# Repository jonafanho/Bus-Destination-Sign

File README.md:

# Bus Destination Sign
A simulation of LED or flip dot bus destination signs using the STM32 Blue Pill.

## Quick Start
### First Run
1. Insert an empty micro SD card (formatted to FAT32) into the SD card slot.
1. Power up the STM32 microcontroller using a Micro USB cable.
1. After the system finishes loading, the screen will turn black. The necessary folders and configuration files will be automatically set up on the SD card.
1. Turn off the microcontroller by unplugging the Micro USB cable, then remove the SD card from the SD card slot.

### Adding Images
1. On a computer, download or obtain images to be shown on the destination signs. Some good sites include [HKBRDA](https://www.hkbrda.org/rddc/main.php) and [Stopreporter](https://sites.google.com/site/stopreporter2003/edisplay).
1. Convert all images into the BMP file format. [Online converter](https://image.online-convert.com/convert-to-bmp) is an easy site to convert images quickly.
1. Open the SD card on the computer. Inside the SD card, you should see the following folders:
   * In the root directory, there should be ten folders named `0` to `9`. These folders group images of the same bus routes together.
   * In each of the ten folders, there should be three folders named `front`, `side`, and `back`. These folders designate which images appear on the front, side, and rear displays.
   * If these folders don't exist, follow the [First Run](#first-run) steps above to automatically create the necessary folders and configuration files.
1. Copy the BMP files to any of the `front`, `side`, or `back` folders on the SD card.
   * Images of the same bus route should be grouped together.
   * Images of the front, side, and back displays should go into their respective folders.
   * An example of the SD card file structure is shown [below](#example-sd-card-file-structure).
1. Safely eject the SD card from the computer and reinsert the SD card to the SD card slot.
1. Power up the STM32 microcontroller again.
   * The images from `0/front`, `0/side`, and `0/back` should show up on the front, side, and back displays respectively.
   * On the device or a connected remote, press the button to change routes. The images from `1/front`, `1/side`, and `1/back` should now show up.
   * Pressing the button again should cycle thorugh the routes. Note that if all three `front`, `side`, and `back` folders of a group is empty, the group will be skipped.

### Example SD Card File Structure
```
root
├───global_settings.txt
├───0
│   ├───image_settings.txt
│   ├───front
│   │   ├───KMB-74X-00.bmp
│   │   └───KMB-74X-01.bmp
│   ├───side
│   │   └───KMB-74X-10.bmp
│   └───back
│       └───KMB-74X-20.bmp
├───1
│   ├───image_settings.txt
│   ├───front
│   │   ├───KMB-680-00.bmp
│   │   ├───KMB-680-01.bmp
│   │   └───KMB-680-02.bmp
│   ├───side
│   │   ├───KMB-680-10.bmp
│   │   └───KMB-680-11.bmp
│   └───back
│       ├───KMB-680-20.bmp
│       └───KMB-680-21.bmp
...
└───9
    ├───image_settings.txt
    ├───front
    │   └───KMB-special-00.bmp
    ├───side
    └───back
```

## Configuration
There are two types of settings that can be configured by the user. All fields accept positive integers. If a corrupted settings file is detected, it will be reset to its default values.

### Global Settings
These settings control the display animation as a whole. The configuration file, `global_settings.txt`, is in the root of the SD card.

The contents of `global_settings.txt` with its default values are shown below.
```
scroll_animation=1
switch_delay=2
```
Parameter | Description
--- | ---
`scroll_animation` | Defines whether a scrolling animation will be used when switching between images. The scrolling animation simulates flip dot displays.<br>`scroll_animation=0`: No scrolling animation<br>`scroll_animation=1`: Scrolling animation
`switch_delay` | The amount of time (in seconds) to show each image before switching to the next one.<br>Note: The actual time might be greater than the number specified here depending on the time it takes to load the next image.

### Image Settings
These settings control the way images are scaled or cropped. The configuration file, `image_settings.txt`, is inside each of the ten folders `0` to `9` on the SD card.

"Scale" refers to how many pixels (in one axis) on the BMP image maps to one pixel (in one axis) on the physical display. For example, a scale of 3 means that every 3x3 square on the BMP image corresponds to one pixel on the physical display.

"Crop" refers to how many pixels (symmetrical on all sides) of the BMP image will not be shown on the physical display.

The contents of `image_settings.txt` with its default values are shown below.
```
front_scale=3
front_crop=20
side_scale=3
side_crop=19
back_scale=1
back_crop=0
```
Parameter | Description
--- | ---
`front_scale` | The scaling of the images on the front display.
`front_crop` | The crop of the images on the front display.
`side_scale` | The scaling of the images on the side display.
`side_crop` | The crop of the images on the side display.
`back_scale` | The scaling of the images on the back display.
`back_crop` | The crop of the images on the back display.

## Special Scrolling
To use special scrolling on an image, the file name must begin with an exclamation mark (`!`).

After the exclamation mark, the file name should contain a three digit number. This number corresponds to the number of pixels from the left edge (after scaling) where the image should be split. The pixels before the split to the left will display as a stationary image, and the pixels on or after the split to the right will be scrolled. If the number is less than three digits long, it should be padded by zeros.

An example of file names implementing special scrolling is shown below.
```
!046-NWFB-682.bmp
!112-NWFB-15.bmp
```

## Troubleshooting
* My images are not showing up!
  * Make sure the images are in BMP format. (8, 16, 24, and 32-bit uncompressed BMP files are supported.)
  * Make sure the BMP files are in any of the three folders (front, side, or back). They shouldn't be anywhere else or nested inside those folders.
  * Make sure the image crop value is low enough that at least a part of the image is still visible.
* My images take forever to load!
  * Keep the image sizes small, preferably smaller than 500x500 pixels.
  * Images will load slower for the first time as the cache is being created.
* My SD card failed to initalize!
  * Make sure the SD card is formatted to FAT32.
  * Make sure the SD card is clean, inserted fully into the SD card slot, and oriented in the correct direction.

## Building it Yourself
Refer to the [Installation](https://github.com/jonafanho/Bus-Destination-Sign/blob/master/Installation.md) page for instructions.

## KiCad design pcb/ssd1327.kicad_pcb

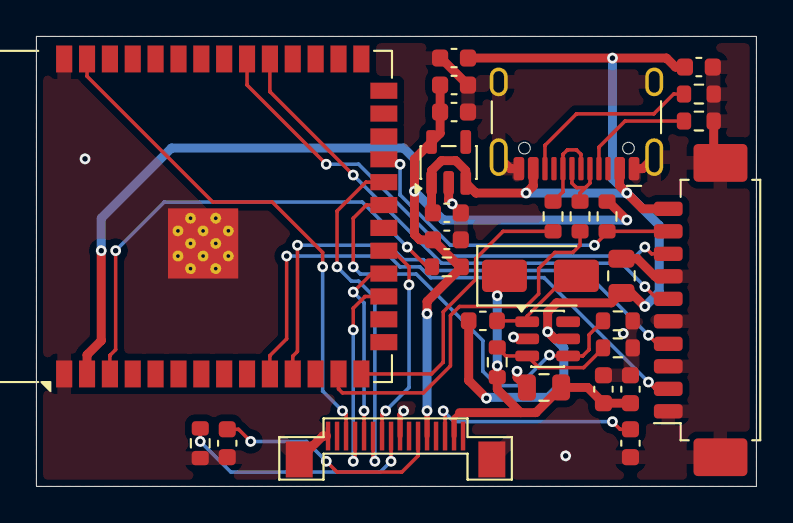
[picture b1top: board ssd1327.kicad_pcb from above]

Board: 2 copper layers, 40.0 x 25.0 mm, 30 parts (0 on the bottom side), 27 nets.

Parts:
C1, C5: 1uF; C_0603_1608Metric
C2: 4.7uF; C_0603_1608Metric
C3, C7, C11: 10uF; C_0603_1608Metric
C4, C8, C12: 0.1uF; C_0603_1608Metric
C6: 2.2uF; C_0603_1608Metric
C9, C10: 22uF; C_0805_2012Metric
D1: SS34; D_SMA
J1: Display Connector Input; Molex_PicoBlade_53261-1071_1x10-1MP_P1.25mm_Horizontal
J2: SSD1327 16-Pin Connector; 16-pin
J3: USB_C_Receptacle_USB2.0_16P; USB_C_Receptacle_HCTL_HC-TYPE-C-16P-01A
L1: 10uH; L_0603_1608Metric
R1, R7, R10: 10k; R_0603_1608Metric
R2: 1M; R_0603_1608Metric
R3, R4: 5.1k; R_0603_1608Metric
R5, R6: 22R; R_0603_1608Metric
R8: 100k; R_0603_1608Metric
R9: 200k; R_0603_1608Metric
U1: AP2112K-3.3; SOT-23-5
U2: ESP32-S3-WROOM-1
U3: MT3608; SOT-23-6

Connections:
+5V: C3.1, C4.1, C5.1, C9.1, J1.10 (5V), J3.A4 (VBUS), J3.A9 (VBUS), J3.B4 (VBUS), J3.B9 (VBUS), L1.1, U1.1 (VIN), U1.3 (EN), U3.5 (IN)
/ESP32 for SSD1327/3V3: C6.1, C7.1, C8.1, J2.5 (VCI), R1.1, R7.1, U1.5 (VOUT), U2.2 (3V3)
/ESP32 for SSD1327/CLK: J1.2 (CLK), U2.10 (IO17)
/ESP32 for SSD1327/GPIO1: J2.14 (MOSI), U2.39 (IO1)
/ESP32 for SSD1327/GPIO9: J2.13 (CLK), U2.17 (IO9)
/ESP32 for SSD1327/GPIO10: J2.12 (DC), U2.18 (IO10)
/ESP32 for SSD1327/GPIO11: J2.10 (CS), U2.19 (IO11)
/ESP32 for SSD1327/GPIO13: R8.1, U2.21 (IO13), U3.4 (EN)
/ESP32 for SSD1327/GPIO14: J2.11 (RES), U2.22 (IO14)
/ESP32 for SSD1327/GPIO21: J1.9 (WAKE), R1.2, U2.23 (IO21)
/ESP32 for SSD1327/GPIO39: J1.8 (CS), U2.32 (IO39)
/ESP32 for SSD1327/MISO: J1.6 (MISO), U2.31 (IO38)
/ESP32 for SSD1327/MOSI: J1.4 (MOSI), U2.11 (IO18)
/MT3608 for SSD1327/12V: C10.1, C11.1, C12.1, D1.1 (K), J2.2 (VCC), R9.1
GND: C1.2, C2.2, C3.2, C4.2, C5.2, C6.2, C7.2, C8.2, C9.2, C10.2, C11.2, C12.2, J1.1 (GND), J1.3 (GND), J1.5 (GND), J1.7 (GND), J1.MP (GND), J2.0 (GND), J2.8 (VSS), J2.16 (VSS), J3.A1 (GND), J3.A12 (GND), J3.B1 (GND), J3.B12 (GND), J3.SH (SHIELD), R2.1, R3.2, R4.2, R8.2, R10.2, U1.2 (GND), U2.1 (GND), U2.40 (GND), U2.41 (GND), U3.2 (GND)
unnamed: D1.2 (A), L1.2, U3.1 (SW)
unnamed: J2.9 (IREF), R2.2
unnamed: C2.1, J2.3 (VCOMH)
unnamed: C1.1, J2.6 (VDD)
unnamed: J3.A5 (CC1), R4.1
unnamed: J3.B5 (CC2), R3.1
unnamed: J3.A6 (D+), J3.B6 (D+), R6.1
unnamed: J3.A7 (D-), J3.B7 (D-), R5.1
unnamed: R7.2, U2.3 (EN)
unnamed: R6.2, U2.14 (USB_D+)
unnamed: R5.2, U2.13 (USB_D-)
unnamed: R9.2, R10.1, U3.3 (FB)

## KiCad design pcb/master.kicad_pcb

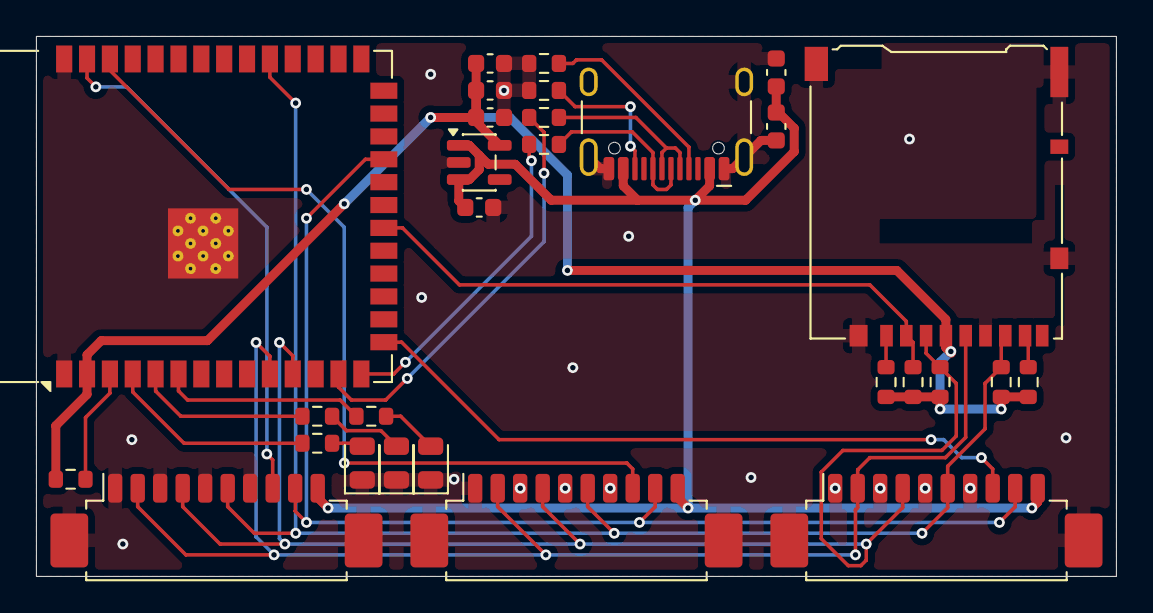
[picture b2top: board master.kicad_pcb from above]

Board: 2 copper layers, 60.0 x 30.0 mm, 29 parts (0 on the bottom side), 26 nets.

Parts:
C1, C5: 10uF; C_0603_1608Metric
C2, C6: 0.1uF; C_0603_1608Metric
C3: 1uF; C_0603_1608Metric
C4: 2.2uF; C_0603_1608Metric
D1: Green LED; LED_0805_2012Metric
D2: Yellow LED; LED_0805_2012Metric
D3: Red LED; LED_0805_2012Metric
J1: Micro_SD_Card_Det2; microSD_HC_Hirose_DM3AT-SF-PEJM5
J2, J3, J4: Display Connector Output; Molex_PicoBlade_53261-1071_1x10-1MP_P1.25mm_Horizontal
J5: USB_C_Receptacle_USB2.0_16P; USB_C_Receptacle_HCTL_HC-TYPE-C-16P-01A
R1, R2, R4, R5, R6, R13: 10k; R_0603_1608Metric
R3, R7, R8: 470R; R_0603_1608Metric
R9, R10: 5.1k; R_0603_1608Metric
R11, R12: 22R; R_0603_1608Metric
U1: AP2112K-3.3; SOT-23-5
U2: ESP32-S3-WROOM-1

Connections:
+5V: C1.1, C2.1, C3.1, J2.10 (5V), J3.10 (5V), J4.10 (5V), J5.A4 (VBUS), J5.A9 (VBUS), J5.B4 (VBUS), J5.B9 (VBUS), U1.1 (VIN), U1.3 (EN)
/CLK: J1.5 (CLK), J2.2 (CLK), J3.2 (CLK), J4.2 (CLK), U2.10 (IO17)
/CS_DISPLAY_1: J2.8 (CS), U2.39 (IO1)
/CS_DISPLAY_2: J3.8 (CS), U2.38 (IO2)
/CS_DISPLAY_3: J4.8 (CS), U2.15 (IO3)
/MISO: J1.7 (DAT0), J2.6 (MISO), J3.6 (MISO), J4.6 (MISO), R2.2, U2.31 (IO38)
/MOSI: J1.3 (CMD), J2.4 (MOSI), J3.4 (MOSI), J4.4 (MOSI), R4.2, U2.11 (IO18)
/Master ESP32/3V3: C4.1, C5.1, C6.1, J1.4 (VDD), R1.1, R2.1, R4.1, R5.1, R6.1, R13.1, U1.5 (VOUT), U2.2 (3V3)
/Master ESP32/GPIO4: R8.2, U2.4 (IO4)
/Master ESP32/GPIO5: R7.2, U2.5 (IO5)
/Master ESP32/GPIO6: R3.2, U2.6 (IO6)
/Master ESP32/GPIO12: J1.2 (DAT3/CD), R5.2, U2.20 (IO12)
/WAKE: J2.9 (WAKE), J3.9 (WAKE), J4.9 (WAKE), U2.23 (IO21)
GND: C1.2, C2.2, C3.2, C4.2, C5.2, C6.2, D1.1 (K), D2.1 (K), D3.1 (K), J1.6 (VSS), J2.1 (GND), J2.3 (GND), J2.5 (GND), J2.7 (GND), J2.MP (GND), J3.1 (GND), J3.3 (GND), J3.5 (GND), J3.7 (GND), J3.MP (GND), J4.1 (GND), J4.3 (GND), J4.5 (GND), J4.7 (GND), J4.MP (GND), J5.A1 (GND), J5.A12 (GND), J5.B1 (GND), J5.B12 (GND), R9.2, R10.2, U1.2 (GND), U2.1 (GND), U2.40 (GND), U2.41 (GND)
unnamed: D1.2 (A), R3.1
unnamed: D2.2 (A), R7.1
unnamed: D3.2 (A), R8.1
unnamed: J1.8 (DAT1), R1.2
unnamed: J1.1 (DAT2), R6.2
unnamed: J5.A5 (CC1), R10.1
unnamed: J5.B5 (CC2), R9.1
unnamed: J5.A6 (D+), J5.B6 (D+), R12.1
unnamed: J5.A7 (D-), J5.B7 (D-), R11.1
unnamed: R13.2, U2.3 (EN)
unnamed: R12.2, U2.14 (USB_D+)
unnamed: R11.2, U2.13 (USB_D-)

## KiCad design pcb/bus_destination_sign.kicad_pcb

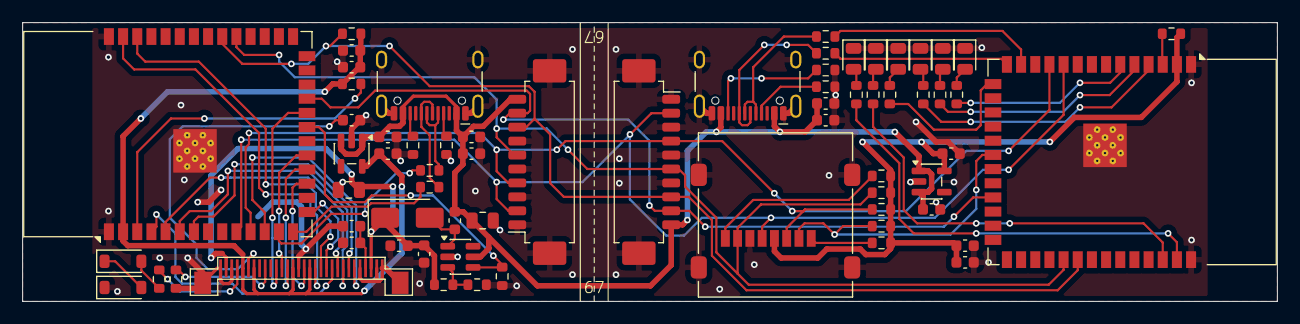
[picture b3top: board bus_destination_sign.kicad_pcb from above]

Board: 2 copper layers, 112.5 x 25.0 mm, 67 parts (0 on the bottom side), 60 nets.

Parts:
C1, C3, C14: 1uF; C_0603_1608Metric
C2, C15: 2.2uF; C_0603_1608Metric
C4: 4.7uF (25V); C_0603_1608Metric
C5, C7: 0.1uF (25V); C_0603_1608Metric
C6: 10uF (25V); C_0603_1608Metric
C8: 22uF; C_0805_2012Metric
C9: 22uF (25V); C_0805_2012Metric
C10, C12, C16, C18: 10uF; C_0603_1608Metric
C11, C13, C17, C19: 0.1uF; C_0603_1608Metric
D1, D2: 1N4148; D_SOD-123
D3: SS34; D_SMA
D4, D7: Red LED; LED_0805_2012Metric
D5, D8: Yellow LED; LED_0805_2012Metric
D6, D9: Green LED; LED_0805_2012Metric
J1, J4: USB_C_Receptacle_USB2.0_16P; USB_C_Receptacle_HCTL_HC-TYPE-C-16P-01A
J2: Display Connector Input; Molex_PicoBlade_53261-1071_1x10-1MP_P1.25mm_Horizontal
J3: SSD1322 30-Pin Connector; ssd1322
J5: Display Connector Output; Molex_PicoBlade_53261-1071_1x10-1MP_P1.25mm_Horizontal
J6: Micro_SD_Card; microSD_HC_Molex_47219-2001
L1: 22uH (or 10uH); L_0603_1608Metric
R1: 910k (or 1M); R_0603_1608Metric
R2: 50R; R_0603_1608Metric
R3: 190k (or 200k); R_0603_1608Metric
R4, R10, R11, R16, R18, R19, R20, R21, R22: 10k; R_0603_1608Metric
R5, R6, R12, R13: 5.1k; R_0603_1608Metric
R7, R8, R14, R15: 22R; R_0603_1608Metric
R9: 100k; R_0603_1608Metric
R23, R24, R25, R26, R27, R28: 470R; R_0603_1608Metric
U1, U5: ESP32-S3-WROOM-1
U2, U4: AP2112K-3.3; SOT-23-5
U3: MT3608; SOT-23-6

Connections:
+5V: C1.1, C8.1, C10.1, C11.1, C14.1, C16.1, C17.1, J1.A4 (VBUS), J1.A9 (VBUS), J1.B4 (VBUS), J1.B9 (VBUS), J2.10 (5V), J4.A4 (VBUS), J4.A9 (VBUS), J4.B4 (VBUS), J4.B9 (VBUS), J5.10 (5V), L1.1, U2.1 (VIN), U2.3 (EN), U3.5 (IN), U4.1 (VIN), U4.3 (EN)
+12V: C6.1, C7.1, C9.1, D3.1 (K), J3.3 (VCC), J3.29 (VCC), R3.1
/CLK: J2.2 (CLK), J5.2 (CLK), J6.5 (CLK), U1.10 (IO17), U5.10 (IO17)
/CS_DISPLAY: J2.8 (CS), J5.8 (CS), R10.2, U1.32 (IO39), U5.32 (IO39)
/CS_SD: J6.2 (DAT3/CD), R22.2, U5.20 (IO12)
/ESP32 for SSD1322/3V3: C15.1, C18.1, C19.1, J3.14 (E/RD#), J3.17 (BS1), J3.24 (VDDIO), J3.26 (VCI), R10.1, R16.1, U1.2 (3V3), U2.5 (VOUT)
/ESP32 for SSD1322/GPIO1: J3.13 (D0), U1.39 (IO1)
/ESP32 for SSD1322/GPIO2: J3.12 (D1), U1.38 (IO2)
/ESP32 for SSD1322/GPIO3: J3.11 (D2), U1.15 (IO3)
/ESP32 for SSD1322/GPIO4: J3.10 (D3), U1.4 (IO4)
/ESP32 for SSD1322/GPIO5: J3.9 (D4), U1.5 (IO5)
/ESP32 for SSD1322/GPIO6: J3.8 (D5), U1.6 (IO6)
/ESP32 for SSD1322/GPIO7: J3.7 (D6), U1.7 (IO7)
/ESP32 for SSD1322/GPIO8: J3.6 (D7), U1.12 (IO8)
/ESP32 for SSD1322/GPIO9: J3.15 (RW#), U1.17 (IO9)
/ESP32 for SSD1322/GPIO10: J3.18 (DC#), U1.18 (IO10)
/ESP32 for SSD1322/GPIO11: J3.19 (CS#), U1.19 (IO11)
/ESP32 for SSD1322/GPIO13: R9.1, U1.21 (IO13), U3.4 (EN)
/ESP32 for SSD1322/GPIO14: J3.20 (RES#), U1.22 (IO14)
/MISO: J2.6 (MISO), J5.6 (MISO), J6.7 (DAT0), R20.2, U1.31 (IO38), U5.31 (IO38)
/MOSI: J2.4 (MOSI), J5.4 (MOSI), J6.3 (CMD), R19.2, U1.11 (IO18), U5.11 (IO18)
/Master ESP32/3V3: C2.1, C12.1, C13.1, J6.4 (VDD), R11.1, R18.1, R19.1, R20.1, R21.1, R22.1, U4.5 (VOUT), U5.2 (3V3)
/Master ESP32/GPIO1: R23.2, U5.39 (IO1)
/Master ESP32/GPIO2: R24.2, U5.38 (IO2)
/Master ESP32/GPIO3: R25.2, U5.15 (IO3)
/Master ESP32/GPIO4: R26.2, U5.4 (IO4)
/Master ESP32/GPIO5: R27.2, U5.5 (IO5)
/Master ESP32/GPIO6: R28.2, U5.6 (IO6)
/WAKE: J2.9 (WAKE), J5.9 (WAKE), U1.23 (IO21), U5.23 (IO21)
GND: C1.2, C2.2, C3.2, C4.2, C5.2, C6.2, C7.2, C8.2, C9.2, C10.2, C11.2, C12.2, C13.2, C14.2, C15.2, C16.2, C17.2, C18.2, C19.2, D2.1 (K), D4.1 (K), D5.1 (K), D6.1 (K), D7.1 (K), D8.1 (K), D9.1 (K), J1.A1 (GND), J1.A12 (GND), J1.B1 (GND), J1.B12 (GND), J1.S1 (SHIELD), J2.1 (GND), J2.3 (GND), J2.5 (GND), J2.7 (GND), J2.MP (GND), J3.0 (PAD), J3.1, J3.2 (VSS), J3.5 (VLSS), J3.16 (BS0), J3.28 (VLSS), J3.30, J4.A1 (GND), J4.A12 (GND), J4.B1 (GND), J4.B12 (GND), J4.S1 (SHIELD), J5.1 (GND), J5.3 (GND), J5.5 (GND), J5.7 (GND), J5.MP (GND), J6.6 (VSS), J6.9 (SHIELD), R1.1, R4.2, R5.2, R6.2, R9.2, R12.2, R13.2, U1.1 (GND), U1.40 (GND), U1.41 (GND), U2.2 (GND), U3.2 (GND), U4.2 (GND), U5.1 (GND), U5.40 (GND), U5.41 (GND)
unnamed: D1.2 (A), R2.1
unnamed: D1.1 (K), D2.2 (A)
unnamed: D3.2 (A), L1.2, U3.1 (SW)
unnamed: D4.2 (A), R23.1
unnamed: D5.2 (A), R24.1
unnamed: D6.2 (A), R25.1
unnamed: D7.2 (A), R26.1
unnamed: D8.2 (A), R27.1
unnamed: D9.2 (A), R28.1
unnamed: J1.A5 (CC1), R13.1
unnamed: J1.B5 (CC2), R12.1
unnamed: J1.A6 (D+), J1.B6 (D+), R15.1
unnamed: J1.A7 (D-), J1.B7 (D-), R14.1
unnamed: J3.22 (IREF), R1.2
unnamed: C4.1, C5.1, J3.4 (VCOMH)
unnamed: C3.1, J3.25 (VDD)
unnamed: J3.27 (VSL), R2.2
unnamed: J4.A5 (CC1), R6.1
unnamed: J4.B5 (CC2), R5.1
unnamed: J4.A6 (D+), J4.B6 (D+), R8.1
unnamed: J4.A7 (D-), J4.B7 (D-), R7.1
unnamed: J6.8 (DAT1), R21.2
unnamed: J6.1 (DAT2), R18.2
unnamed: R16.2, U1.3 (EN)
unnamed: R15.2, U1.14 (USB_D+)
unnamed: R14.2, U1.13 (USB_D-)
unnamed: R3.2, R4.1, U3.3 (FB)
unnamed: R11.2, U5.3 (EN)
unnamed: R8.2, U5.14 (USB_D+)
unnamed: R7.2, U5.13 (USB_D-)

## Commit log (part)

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2020-01-03 Initial file upload.
2020-01-04 Updated .gitignore to include VS Code.
2020-01-04 Moved and renamed files.
2020-01-04 Added cropping.
2020-01-08 Grouped images into ten folders on the SD card.
2020-01-09 Implemented settings.txt on the SD card for scale and crop.
2020-01-09 Begin testing for multiple display groups.
2020-01-09 Added a main settings file.
2020-01-10 Applied the main settings file.
2020-01-11 Update README.md and the license.
2020-01-11 Renamed settings files.
2020-01-11 Testing fancy scroll for some NWFB/CTB buses.
2020-01-11 Fancy scroll now reads from the image file name.
2020-01-12 Fancy scroll moves from off screen on the right.
2020-07-17 Reformatted for CLion.
2020-07-17 Migrated code for the ESP8266.
2020-07-18 Added a simple webpage using SPIFFS.
2020-07-19 Added basic tabs and file upload to the webpage.
2020-07-20 Added sliders to edit the uploaded image.
2020-07-21 Added scale and zoom for the image.
2020-07-21 Sliders and file input styling.
2020-07-21 Added cropping and improved styling for the interface.
2020-07-22 Updated the image editor.
2020-07-22 Added categories for the different displays.
2020-07-23 Refactored the different displays and fixed crashes.
2020-07-27 Added display selection hover effects and other visual fixes.
2020-07-28 Implemented a test button to send a POST request.
2020-07-28 Test button updates the corresponding screen.
2020-07-28 Small fix to update images when another one is selected.
2020-07-29 Showing MAC address after connecting to WiFi.
2020-08-02 Test button for multiple images.
2020-08-02 Reduced the number of refreshes for images.
2020-08-02 Added some delays and more server handlers in loops.
2020-08-08 Save website state in a settings file.
2020-08-08 Added group switching by web selection.
2020-08-10 Reduced the number of redrawing for an image.
2020-08-10 Upload button uploads all groups at once.
2020-08-14 Temporary fix for file uploading issues.
2020-09-08 Used greyscale images to reduce settings size.
2020-09-09 Fix original image not scaling in the image editor.
2020-09-09 Added a help message for a group.
2020-09-09 Added the slider for fancy scroll.
2020-09-11 Added fancy scrolling.
2020-09-11 Replaced hard coded buffer sizes with constants.
2021-12-29 Fixed fancy scrolling speeding up at the end
2021-12-29 Added a save file option to the website
2021-12-29 Added button control for the display
2025-10-08 Rewrite with Spring Boot, Angular, and PlatformIO
2025-10-11 Image uploading and deleting
2025-10-17 Image editing
2025-10-19 Image preview and ESP serial upload
2025-10-22 Use GraalVM to build executables
2025-10-22 Add Spring AOT
2025-10-22 Added the @RegisterReflection annotation
2025-10-22 Added UNSAFE_ALLOCATED for @RegisterReflection
2025-10-22 Added @ImportRuntimeHints
2025-10-23 Use Launch4j
2025-10-23 Fixed build path
2025-12-17 Updated Angular and added upload button
2026-01-01 First draft of the ESP32 SSD1322 PCB design
2026-01-02 Copy and paste image settings buttons
2026-01-02 Added image groups
2026-01-02 Update Angular dependencies
2026-01-02 Revert "Update Angular dependencies"
    This reverts commit 9592c46d680005fba6df599846213bae49c2e523.
2026-01-11 SD card test
2026-01-11 Updated SPI setup for SD card
2026-01-11 Downgraded SdFat library
2026-01-16 Initial code for the custom PCB with the ESP32
2026-01-17 Added anti-aliasing
2026-01-17 Bump tar from 7.5.2 to 7.5.3 in /website
    Bumps [tar](https://github.com/isaacs/node-tar) from 7.5.2 to 7.5.3.
    - [Release notes](https://github.com/isaacs/node-tar/releases)
    - [Changelog](https://github.com/isaacs/node-tar/blob/main/CHANGELOG.md)
    - [Commits](https://github.com/isaacs/node-tar/compare/v7.5.2...v7.5.3)
    ---
    updated-dependencies:
2026-01-18 Added ESP32 code with SPI library
2026-01-21 Bump tar from 7.5.2 to 7.5.6 in /website
    Bumps [tar](https://github.com/isaacs/node-tar) from 7.5.2 to 7.5.6.
    - [Release notes](https://github.com/isaacs/node-tar/releases)
    - [Changelog](https://github.com/isaacs/node-tar/blob/main/CHANGELOG.md)
    - [Commits](https://github.com/isaacs/node-tar/compare/v7.5.2...v7.5.6)
    ---
    updated-dependencies:
2026-01-22 Bump lodash from 4.17.21 to 4.17.23 in /website
    Bumps [lodash](https://github.com/lodash/lodash) from 4.17.21 to 4.17.23.
    - [Release notes](https://github.com/lodash/lodash/releases)
    - [Commits](https://github.com/lodash/lodash/compare/4.17.21...4.17.23)
    ---
    updated-dependencies:
    - dependency-name: lodash
2026-01-22 ESP32 master and display code
2026-01-23 SD card uploading UI
2026-01-23 Use esp_lcd library for the display driver
2026-01-24 Fix send sequence
2026-01-24 Revert esp_lcd changes
2026-01-26 Reroute SSD1322 PCB
2026-01-28 Added ESP32 master circuit
2026-01-28 Updated LED footprints
2026-01-28 Fixed 3.3V connections and SD card orientation
2026-01-28 Edited pin assignments in the code
2026-01-29 Bump tar from 7.5.2 to 7.5.7 in /website
    Bumps [tar](https://github.com/isaacs/node-tar) from 7.5.2 to 7.5.7.
    - [Release notes](https://github.com/isaacs/node-tar/releases)
    - [Changelog](https://github.com/isaacs/node-tar/blob/main/CHANGELOG.md)
    - [Commits](https://github.com/isaacs/node-tar/compare/v7.5.2...v7.5.7)
    ---
    updated-dependencies:
2026-02-19 Bump tar from 7.5.2 to 7.5.9 in /website
    Bumps [tar](https://github.com/isaacs/node-tar) from 7.5.2 to 7.5.9.
    - [Release notes](https://github.com/isaacs/node-tar/releases)
    - [Changelog](https://github.com/isaacs/node-tar/blob/main/CHANGELOG.md)
    - [Commits](https://github.com/isaacs/node-tar/compare/v7.5.2...v7.5.9)
    ---
    updated-dependencies:
2026-02-28 Bump rollup from 4.53.5 to 4.59.0 in /website
    Bumps [rollup](https://github.com/rollup/rollup) from 4.53.5 to 4.59.0.
    - [Release notes](https://github.com/rollup/rollup/releases)
    - [Changelog](https://github.com/rollup/rollup/blob/master/CHANGELOG.md)
    - [Commits](https://github.com/rollup/rollup/compare/v4.53.5...v4.59.0)
    ---
    updated-dependencies:
2026-03-01 Bump @angular/core from 21.0.5 to 21.1.6 in /website
    Bumps [@angular/core](https://github.com/angular/angular/tree/HEAD/packages/core) from 21.0.5 to 21.1.6.
    - [Release notes](https://github.com/angular/angular/releases)
    - [Changelog](https://github.com/angular/angular/blob/main/CHANGELOG.md)
    - [Commits](https://github.com/angular/angular/commits/v21.1.6/packages/core)
    ---
    updated-dependencies:
2026-03-04 Bump immutable from 5.1.3 to 5.1.5 in /website
    Bumps [immutable](https://github.com/immutable-js/immutable-js) from 5.1.3 to 5.1.5.
    - [Release notes](https://github.com/immutable-js/immutable-js/releases)
    - [Changelog](https://github.com/immutable-js/immutable-js/blob/main/CHANGELOG.md)
    - [Commits](https://github.com/immutable-js/immutable-js/compare/v5.1.3...v5.1.5)
    ---
    updated-dependencies:
2026-03-05 Added LED status lights in the code
2026-03-05 Updated upload flash size in platformio.ini files
2026-03-06 Bump tar from 7.5.2 to 7.5.10 in /website
    Bumps [tar](https://github.com/isaacs/node-tar) from 7.5.2 to 7.5.10.
    - [Release notes](https://github.com/isaacs/node-tar/releases)
    - [Changelog](https://github.com/isaacs/node-tar/blob/main/CHANGELOG.md)
    - [Commits](https://github.com/isaacs/node-tar/compare/v7.5.2...v7.5.10)
    ---
    updated-dependencies:
2026-03-08 Fix byte addition logic in addBytes method
2026-03-11 Added SSD1327 circuit
2026-03-11 Fix MT3608 schematic naming
2026-03-11 Bump tar from 7.5.2 to 7.5.11 in /website
    Bumps [tar](https://github.com/isaacs/node-tar) from 7.5.2 to 7.5.11.
    - [Release notes](https://github.com/isaacs/node-tar/releases)
    - [Changelog](https://github.com/isaacs/node-tar/blob/main/CHANGELOG.md)
    - [Commits](https://github.com/isaacs/node-tar/compare/v7.5.2...v7.5.11)
    ---
    updated-dependencies:
2026-03-12 Split PCB into modules
2026-03-12 SSD1327 PCB routing
2026-03-12 Master board PCB routing
2026-03-14 Bump @angular/compiler from 21.0.5 to 21.2.4 in /website
    Bumps [@angular/compiler](https://github.com/angular/angular/tree/HEAD/packages/compiler) from 21.0.5 to 21.2.4.
    - [Release notes](https://github.com/angular/angular/releases)
    - [Changelog](https://github.com/angular/angular/blob/main/CHANGELOG.md)
    - [Commits](https://github.com/angular/angular/commits/v21.2.4/packages/compiler)
    ---
    updated-dependencies:
2026-03-14 Bump @angular/core from 21.0.5 to 21.2.4 in /website
    Bumps [@angular/core](https://github.com/angular/angular/tree/HEAD/packages/core) from 21.0.5 to 21.2.4.
    - [Release notes](https://github.com/angular/angular/releases)
    - [Changelog](https://github.com/angular/angular/blob/main/CHANGELOG.md)
    - [Commits](https://github.com/angular/angular/commits/v21.2.4/packages/core)
    ---
    updated-dependencies:
2026-03-16 Added a PlatformIO build script
2026-03-16 Rename workflow job name
2026-03-21 Bump flatted from 3.3.3 to 3.4.2 in /website
    Bumps [flatted](https://github.com/WebReflection/flatted) from 3.3.3 to 3.4.2.
    - [Commits](https://github.com/WebReflection/flatted/compare/v3.3.3...v3.4.2)
    ---
    updated-dependencies:
    - dependency-name: flatted
    dependency-version: 3.4.2
2026-03-27 Simplify preprocessor directives
2026-03-28 Rename project and added update workflow
2026-03-28 Manually update packages
2026-03-28 Update Angular packages
2026-03-28 Added Gradle update to the workflow
2026-03-29 Update Gradle and Angular
2026-04-01 Testing file loading with existing displays
2026-04-08 Support for different display types
2026-04-09 Added wipe animation
2026-04-11 Manually update npm packages
2026-04-16 Refactor the stream reader and SPI classes
2026-04-18 Changed the Angular frontend
2026-04-21 Added frontend data persistence
2026-04-27 First draft of the SSD1327 driver
2026-04-30 Improved SPI payload size limit
2026-05-01 Added onboard display scaling
2026-05-01 Fix SSD1327 typo
2026-05-01 Pass CS pin for SPI master and better SD initialization
2026-05-01 Fixed SSD1327 data logic
2026-05-02 Drive multiple displays and added rotation and wipe parameters
2026-05-02 Added pixelated style options
2026-05-02 Use SdFat and Arduino SPI libraries
2026-05-04 Code cleanup and changed binary file format
2026-05-04 Use preprocessors to import the correct display driver
2026-05-05 Various fixes; see description
    - Fixed SD Card zip file directories
    - Fixed preprocessors
    - Generic images now have a default duration
    - Save settings to cookies
    - Auto reboot when initialization fails
2026-05-07 Refactor: Remove SD card for now
2026-05-07 Added SPI footer verification
